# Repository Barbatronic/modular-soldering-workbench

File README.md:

# modular-soldering-workbench
A modular soldering workbench for PCB assembly, offering expandable modules and adaptable tooling for electronics prototyping.

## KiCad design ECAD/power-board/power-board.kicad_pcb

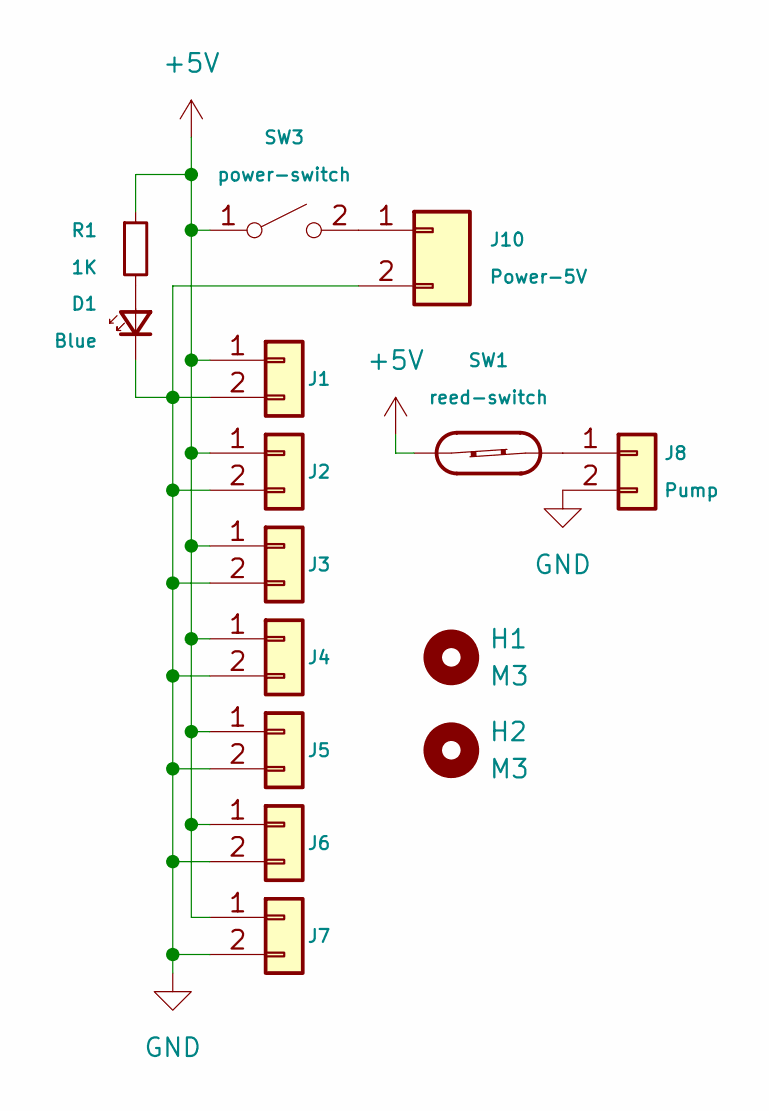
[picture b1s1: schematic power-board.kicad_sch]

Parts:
D1: Blue; LED_D5.0mm_Horizontal_O1.27mm_Z3.0mm
H1, H2: M3; MountingHole_3.2mm_M3
J1, J2, J3, J4, J5, J6, J7: Conn_01x02; JST_XH_B2B-XH-A_1x02_P2.50mm_Vertical
J8: Pump; JST_XH_B2B-XH-A_1x02_P2.50mm_Vertical
J10: Power-5V; Molex_KK-254_AE-6410-02A_1x02_P2.54mm_Vertical
R1: 1K; R_Axial_DIN0207_L6.3mm_D2.5mm_P2.54mm_Vertical
SW1: reed-switch; PinHeader_1x02_P2.54mm_Vertical
SW3: power-switch; PinHeader_1x02_P2.54mm_Vertical

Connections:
+5V: J1.1, J2.1, J3.1, J4.1, J5.1, J6.1, J7.1, R1.1, SW1.1, SW3.1 (A)
GND: D1.1 (K), J1.2, J2.2, J3.2, J4.2, J5.2, J6.2, J7.2, J8.2, J10.2
unnamed: D1.2 (A), R1.2
unnamed: J8.1, SW1.2
unnamed: J10.1, SW3.2 (B)

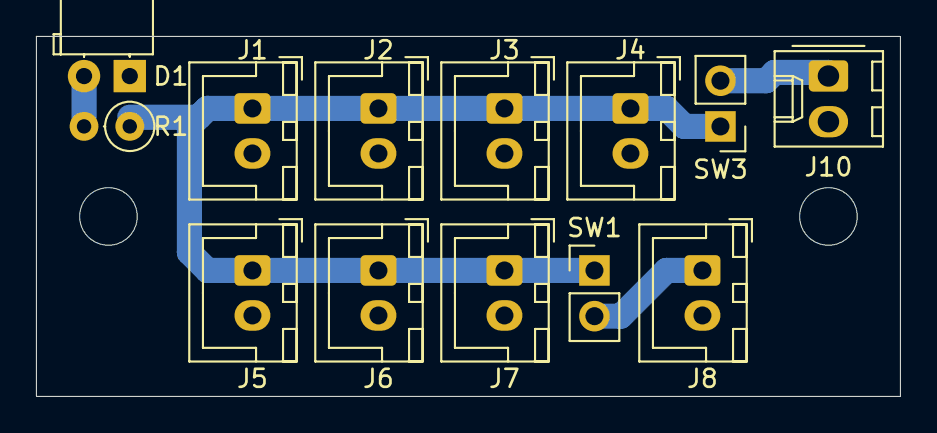
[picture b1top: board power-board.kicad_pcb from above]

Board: 2 copper layers, 48.0 x 20.0 mm, 15 parts (0 on the bottom side), 5 nets.

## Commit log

2025-11-22 Structure with assembly
2025-11-22 adding screws and nuts
2025-11-22 add inner bearing
2025-11-23 add table parts and asm
2025-11-24 new assembly + blower and lock parts
2025-11-25 new blower
2025-11-26 add images
2025-11-28 addon and new assembly version
2025-11-29 new soldering pinecil support and cleaning tip
2025-11-30 update for live
2025-12-01 add fan extractor and spool holder
2025-12-01 WIP - New spool
2025-12-06 add new spool holder
2025-12-14 Update parts design files - add pump and pick and place pen
2025-12-14 Update pump support and pen
2026-01-04 power board - PCB laser design
2026-01-04 add carter
2026-01-11 live 250
